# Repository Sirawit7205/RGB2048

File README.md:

# Board2048
Play 2048 on RGB LED matrix!

Hardware is licensed under `SPDX-License-Identifier: Apache-2.0 WITH SHL-2.1`

Software is licensed under `SPDX-License-Identifier: Apache-2.0`

Documentation is licensed under `SPDX-License-Identifier: CC-BY-SA-4.0`

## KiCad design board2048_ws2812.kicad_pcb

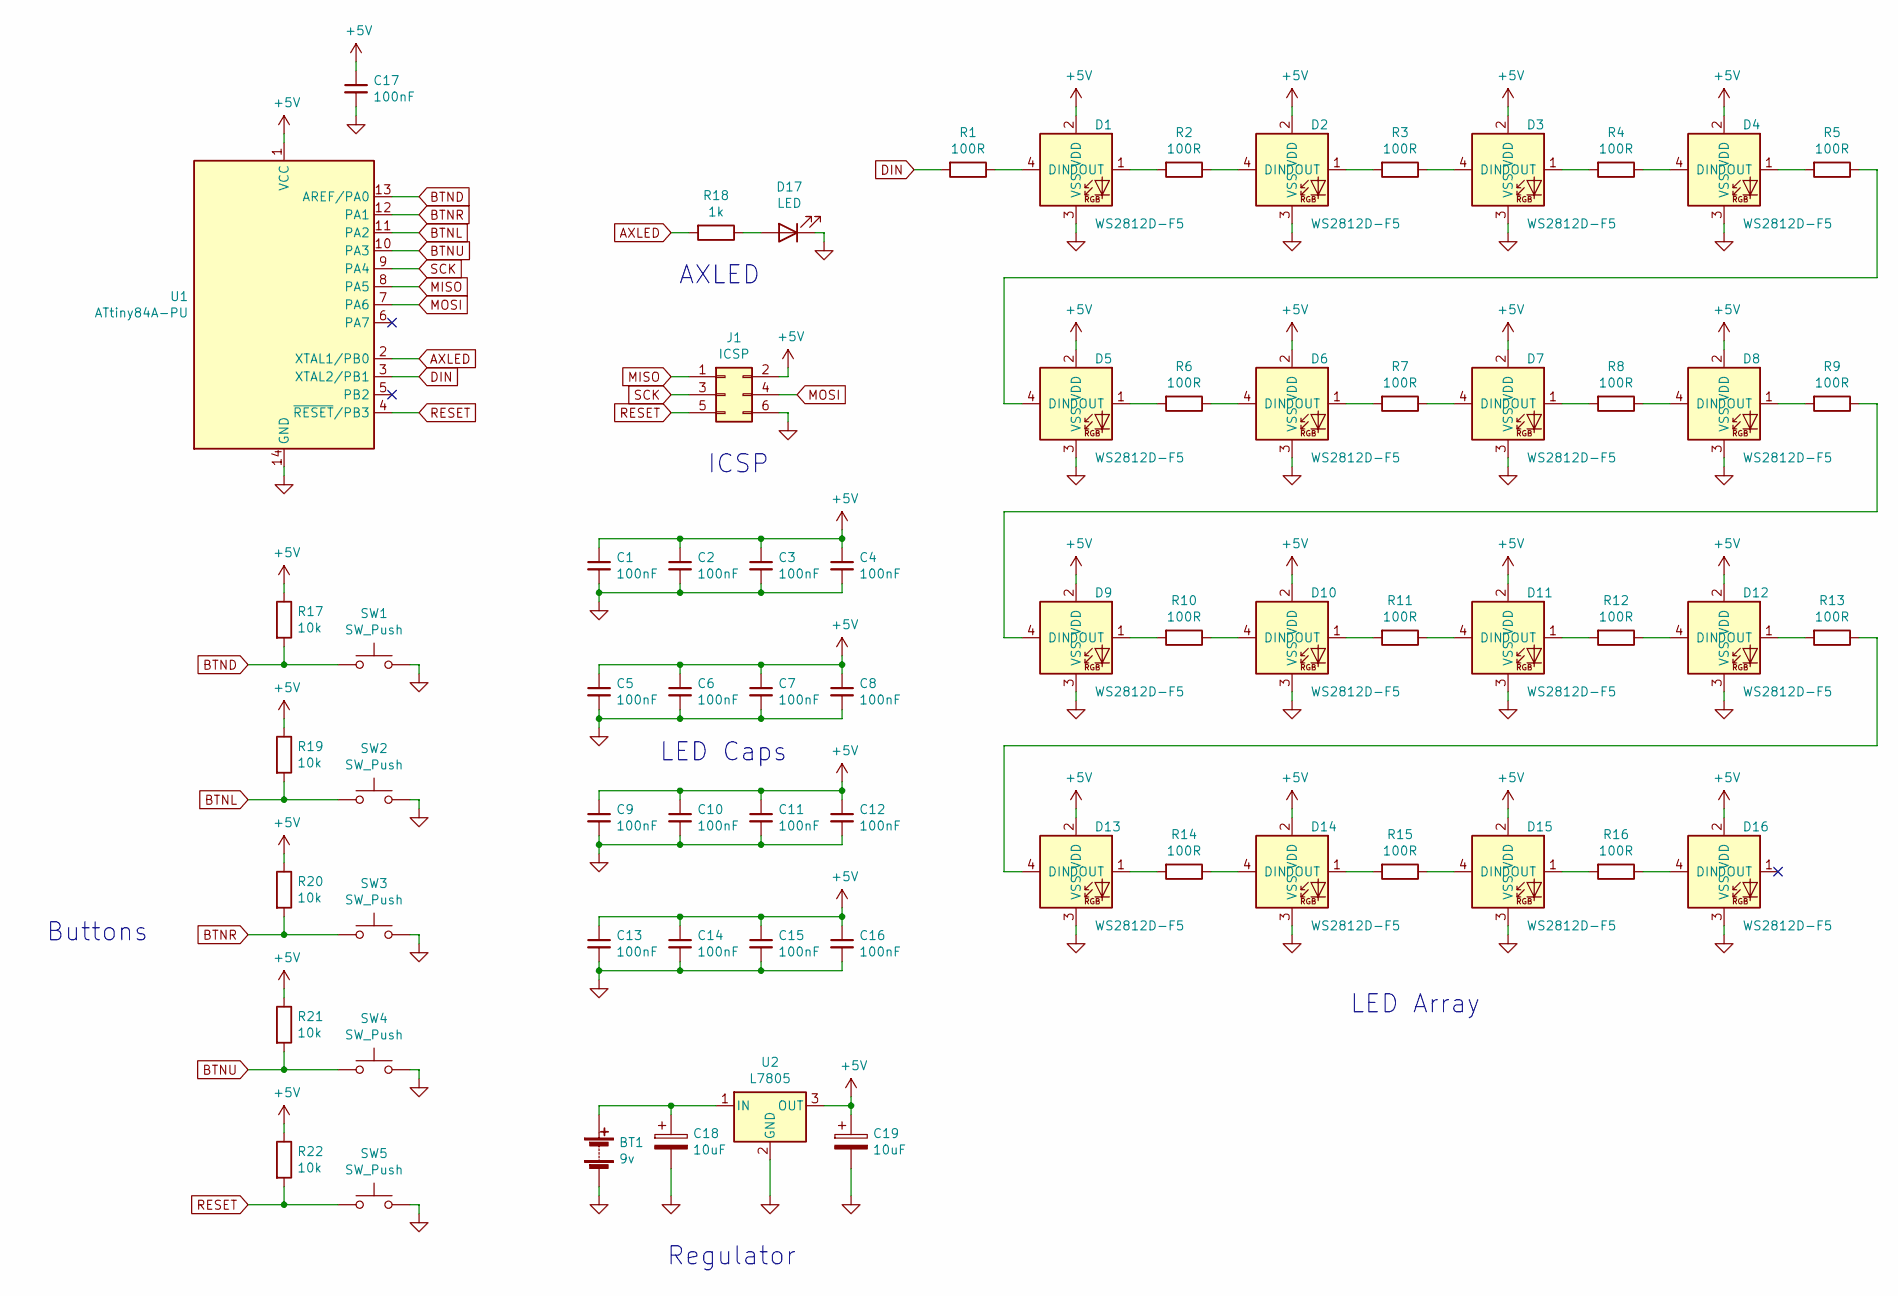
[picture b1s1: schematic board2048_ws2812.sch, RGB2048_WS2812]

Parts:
BT1: 9v; PinHeader_1x02_P2.54mm_Vertical
C1, C2, C3, C4, C5, C6, C7, C8, C9, C10, C11, C12, C13, C14, C15, C16, C17: 100nF; C_Disc_D5.0mm_W2.5mm_P2.50mm
C18, C19: 10uF; CP_Radial_D5.0mm_P2.00mm
D1, D2, D3, D4, D5, D6, D7, D8, D9, D10, D11, D12, D13, D14, D15, D16: WS2812D-F5; LED_D5.0mm-4_RGB
D17: LED; LED_D5.0mm
J1: ICSP; PinHeader_2x03_P2.54mm_Vertical
R1, R2, R3, R4, R5, R6, R7, R8, R9, R10, R11, R12, R13, R14, R15, R16: 100R; R_Axial_DIN0204_L3.6mm_D1.6mm_P5.08mm_Horizontal
R17, R19, R20, R21, R22: 10k; R_Axial_DIN0204_L3.6mm_D1.6mm_P5.08mm_Horizontal
R18: 1k; R_Axial_DIN0204_L3.6mm_D1.6mm_P5.08mm_Horizontal
SW1, SW2, SW3, SW4, SW5: SW_Push; SW_PUSH_6mm
U1: ATtiny84A-PU; DIP-14_W7.62mm
U2: L7805; TO-220-3_Vertical

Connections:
+5V: C1.1, C2.1, C3.1, C4.1, C5.1, C6.1, C7.1, C8.1, C9.1, C10.1, C11.1, C12.1, C13.1, C14.1, C15.1, C16.1, C17.1, C19.1, D1.2 (VDD), D2.2 (VDD), D3.2 (VDD), D4.2 (VDD), D5.2 (VDD), D6.2 (VDD), D7.2 (VDD), D8.2 (VDD), D9.2 (VDD), D10.2 (VDD), D11.2 (VDD), D12.2 (VDD), D13.2 (VDD), D14.2 (VDD), D15.2 (VDD), D16.2 (VDD), J1.2, R17.1, R19.1, R20.1, R21.1, R22.1, U1.1 (VCC), U2.3 (OUT)
AXLED: R18.2, U1.2 (XTAL1/PB0)
BTND: R17.2, SW1.1, U1.13 (AREF/PA0)
BTNL: R19.2, SW2.1, U1.11 (PA2)
BTNR: R20.2, SW3.1, U1.12 (PA1)
BTNU: R21.2, SW4.1, U1.10 (PA3)
DIN: R1.2, U1.3 (XTAL2/PB1)
GND: BT1.2 (-), C1.2, C2.2, C3.2, C4.2, C5.2, C6.2, C7.2, C8.2, C9.2, C10.2, C11.2, C12.2, C13.2, C14.2, C15.2, C16.2, C17.2, C18.2, C19.2, D1.3 (VSS), D2.3 (VSS), D3.3 (VSS), D4.3 (VSS), D5.3 (VSS), D6.3 (VSS), D7.3 (VSS), D8.3 (VSS), D9.3 (VSS), D10.3 (VSS), D11.3 (VSS), D12.3 (VSS), D13.3 (VSS), D14.3 (VSS), D15.3 (VSS), D16.3 (VSS), D17.1 (K), J1.6, SW1.2, SW2.2, SW3.2, SW4.2, SW5.2, U1.14 (GND), U2.2 (GND)
MISO: J1.1, U1.8 (PA5)
MOSI: J1.4, U1.7 (PA6)
unnamed: BT1.1 (+), C18.1, U2.1 (IN)
unnamed: D1.1 (DOUT), R2.2
unnamed: D1.4 (DIN), R1.1
unnamed: D2.1 (DOUT), R3.2
unnamed: D2.4 (DIN), R2.1
unnamed: D3.1 (DOUT), R4.2
unnamed: D3.4 (DIN), R3.1
unnamed: D4.1 (DOUT), R5.2
unnamed: D4.4 (DIN), R4.1
unnamed: D5.1 (DOUT), R6.2
unnamed: D5.4 (DIN), R5.1
unnamed: D6.1 (DOUT), R7.2
unnamed: D6.4 (DIN), R6.1
unnamed: D7.1 (DOUT), R8.2
unnamed: D7.4 (DIN), R7.1
unnamed: D8.1 (DOUT), R9.2
unnamed: D8.4 (DIN), R8.1
unnamed: D9.1 (DOUT), R10.2
unnamed: D9.4 (DIN), R9.1
unnamed: D10.1 (DOUT), R11.2
unnamed: D10.4 (DIN), R10.1
unnamed: D11.1 (DOUT), R12.2
unnamed: D11.4 (DIN), R11.1
unnamed: D12.1 (DOUT), R13.2
unnamed: D12.4 (DIN), R12.1
unnamed: D13.1 (DOUT), R14.2
unnamed: D13.4 (DIN), R13.1
unnamed: D14.1 (DOUT), R15.2
unnamed: D14.4 (DIN), R14.1
unnamed: D15.1 (DOUT), R16.2
unnamed: D15.4 (DIN), R15.1
unnamed: D16.4 (DIN), R16.1
unnamed: D17.2 (A), R18.1
RESET: J1.5, R22.2, SW5.1, U1.4 (~RESET~/PB3)
SCK: J1.3, U1.9 (PA4)

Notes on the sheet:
AXLED
Buttons
Regulator
LED Array
ICSP
LED Caps

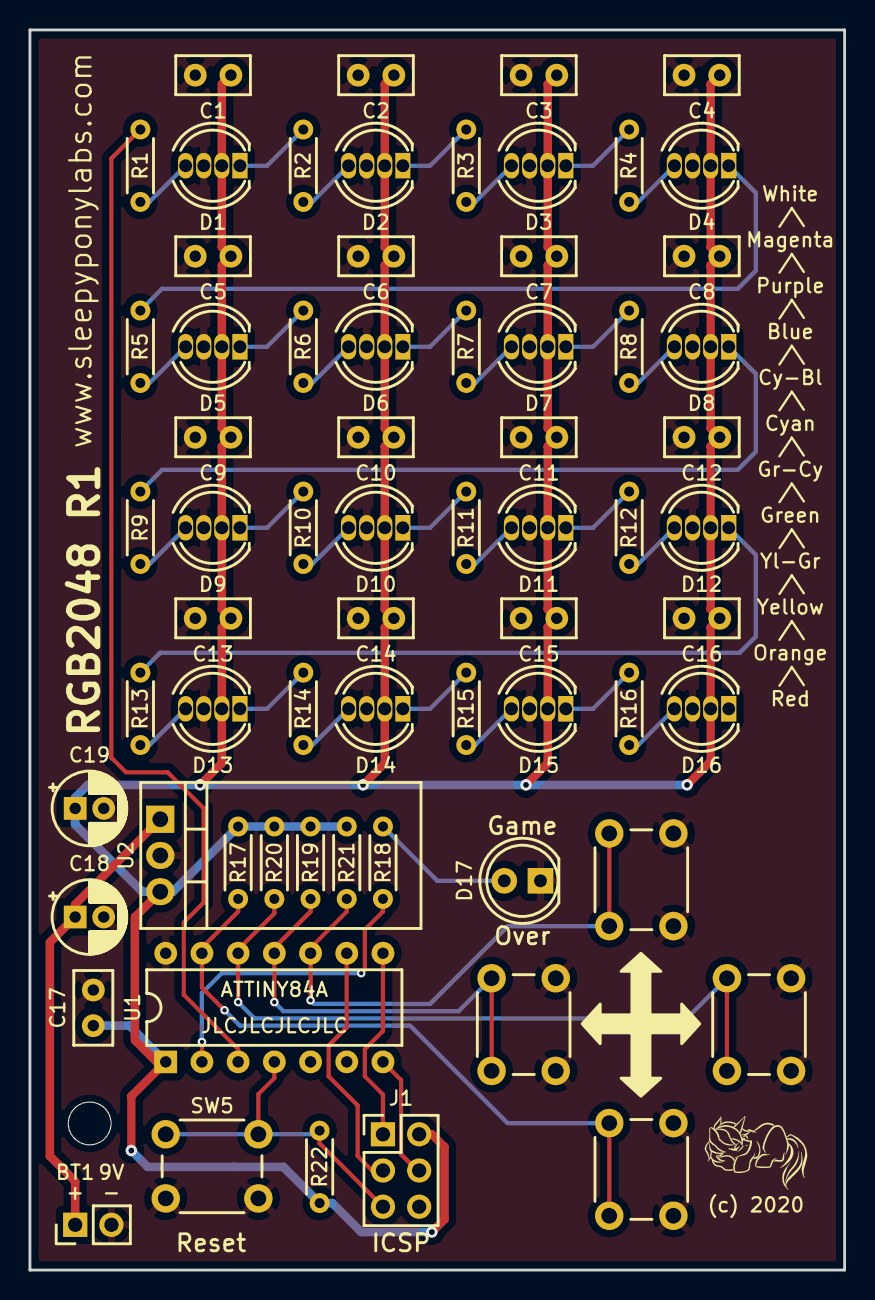
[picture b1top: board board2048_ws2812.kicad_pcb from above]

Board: 2 copper layers, 57.1 x 87.0 mm, 67 parts (0 on the bottom side), 45 nets.

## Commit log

2020-11-04 Edit .gitignore to include vscode part
2020-11-04 Edit .gitignore
2020-11-04 Add Kicad project and code files
2020-11-04 Remove unused files
2020-12-25 Create LICENSE
2023-04-17 Add Arduino Upload Config

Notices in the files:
board2048_ws2812.kicad_pcb:
(c) 2020
